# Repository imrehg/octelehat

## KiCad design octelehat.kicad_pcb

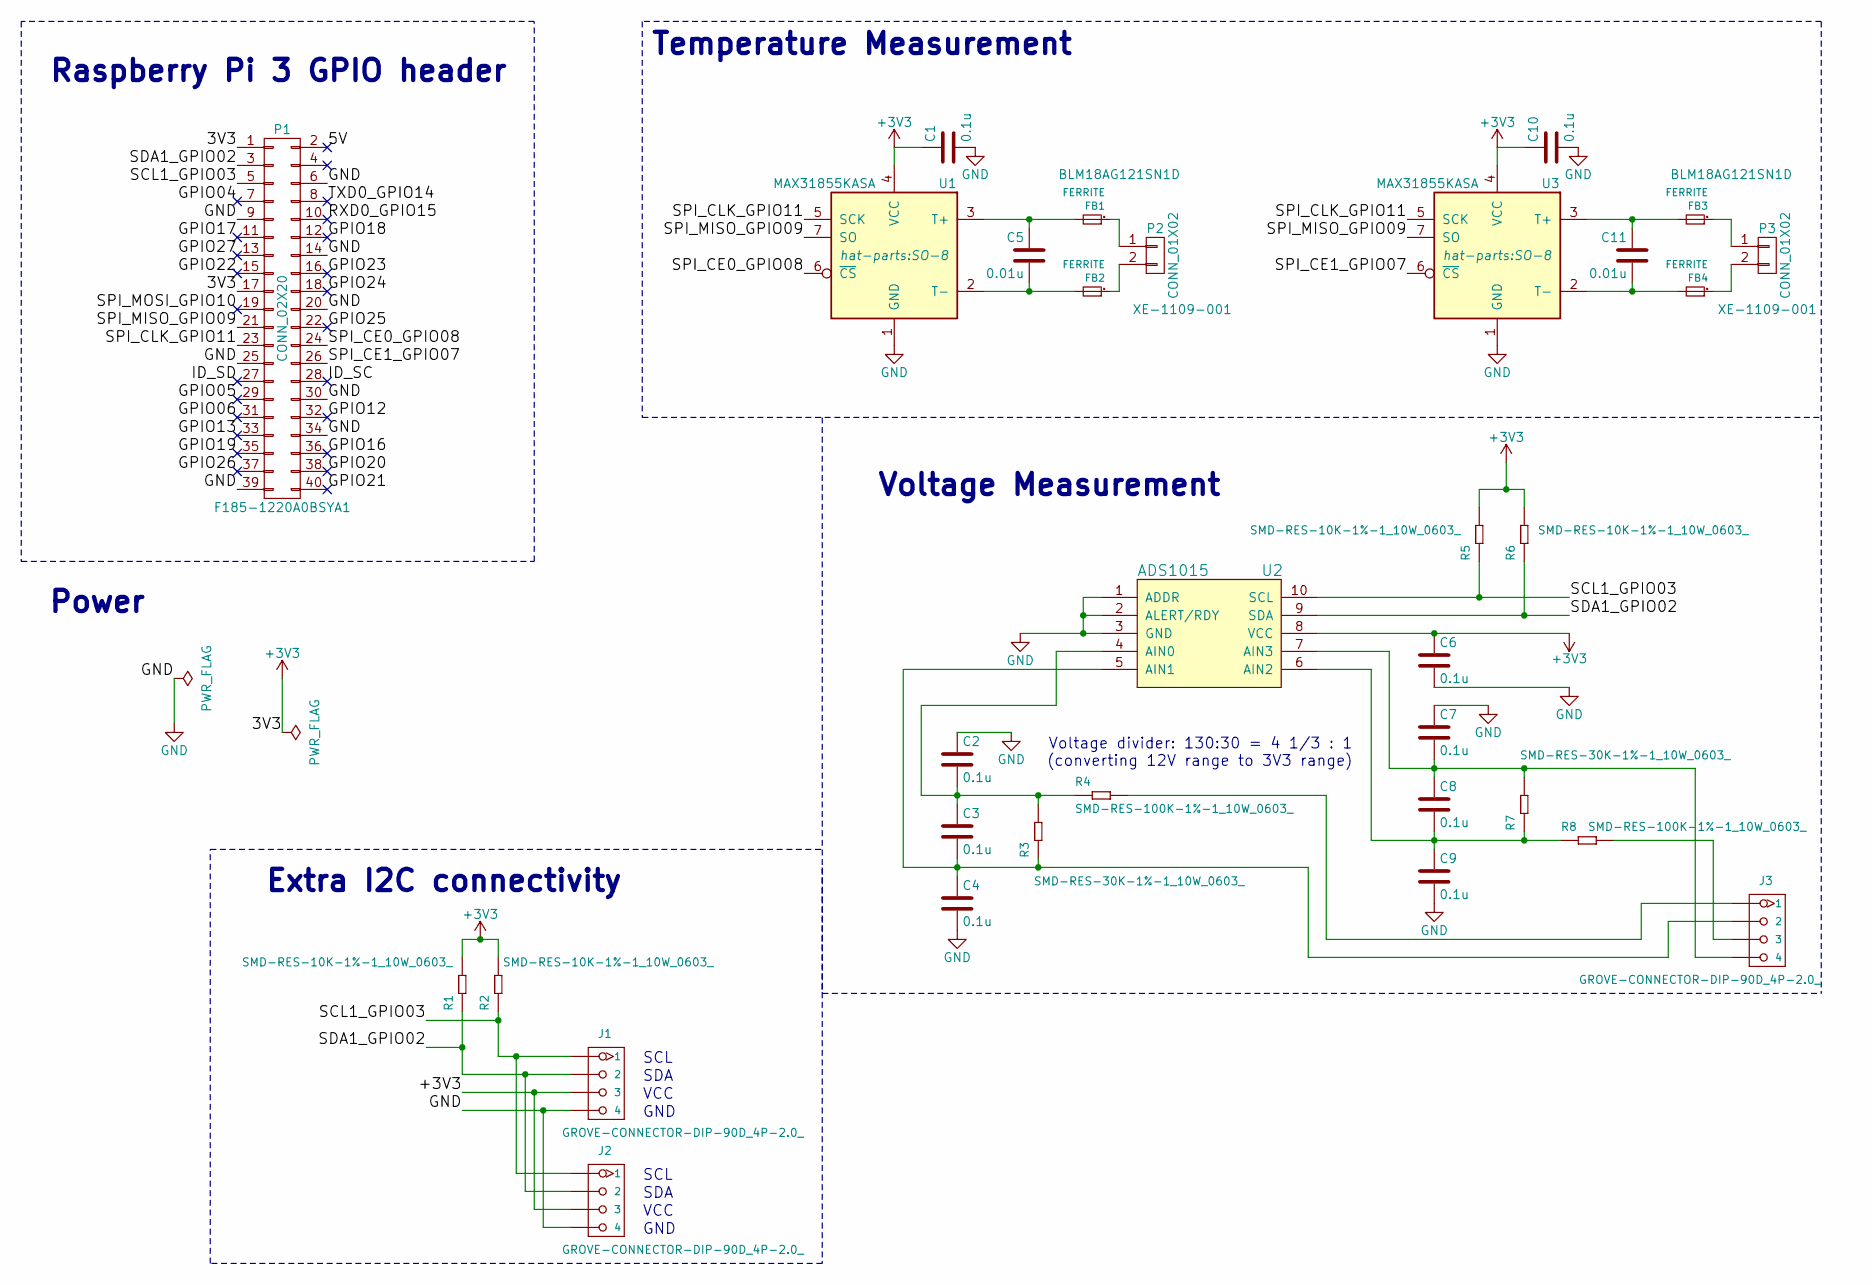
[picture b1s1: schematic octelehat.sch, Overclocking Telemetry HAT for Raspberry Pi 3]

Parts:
C1, C2, C3, C4, C6, C7, C8, C9, C10: 0.1u; C_0402; MPN CC0402KRX7R8BB104
C5, C11: 0.01u; C_0402; MPN CC0402KRX7R9BB103
FB1, FB2, FB3, FB4: FERRITE; L0603; MPN BLM18AG121SN1D
J1, J2, J3: GROVE-CONNECTOR-DIP-90D_4P-2.0_; HW4-2.0-90D; MPN 1125R-4P
P1: CONN_02X20; Socket_Strip_Straight_2x20_Pitch2.54mm; MPN F185-1220A0BSYA1
P2, P3: CONN_01X02; Thermocouple; MPN XE-1109-001
R1, R2, R5, R6: SMD-RES-10K-1%-1_10W_0603_; R0603; MPN RC0603FR-0710KL
R3, R7: SMD-RES-30K-1%-1_10W_0603_; MPN RC0603FR-0730KL
R4, R8: SMD-RES-100K-1%-1_10W_0603_; MPN RC0603FR-07100KL
U1, U3: MAX31855KASA; SO-8; MPN MAX31855KASA
U2: ADS1015; TSSOP-10_3x3mm_Pitch0.5mm; MPN ADS1015IDGSR

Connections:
+3V3: C1.1, C6.1, C10.1, J1.3, J2.3, P1.1, P1.17, R1.2, R2.2, R5.2, R6.2, U1.4 (VCC), U2.8 (VCC), U3.4 (VCC)
/5V: P1.2
/GPIO04: P1.7
/GPIO05: P1.29
/GPIO06: P1.31
/GPIO12: P1.32
/GPIO13: P1.33
/GPIO16: P1.36
/GPIO17: P1.11
/GPIO18: P1.12
/GPIO19: P1.35
/GPIO20: P1.38
/GPIO21: P1.40
/GPIO22: P1.15
/GPIO23: P1.16
/GPIO24: P1.18
/GPIO25: P1.22
/GPIO26: P1.37
/GPIO27: P1.13
/ID_SC: P1.28
/ID_SD: P1.27
/RXD0_GPIO15: P1.10
/SCL1_GPIO03: J1.1, J2.1, P1.5, R2.1, R5.1, U2.10 (SCL)
/SDA1_GPIO02: J1.2, J2.2, P1.3, R1.1, R6.1, U2.9 (SDA)
/SPI_CE0_GPIO08: P1.24, U1.6 (~CS~)
/SPI_CE1_GPIO07: P1.26, U3.6 (~CS~)
/SPI_CLK_GPIO11: P1.23, U1.5 (SCK), U3.5 (SCK)
/SPI_MISO_GPIO09: P1.21, U1.7 (SO), U3.7 (SO)
/SPI_MOSI_GPIO10: P1.19
/TXD0_GPIO14: P1.8
GND: C1.2, C2.1, C4.2, C6.2, C7.1, C9.2, C10.2, J1.4, J2.4, P1.6, P1.9, P1.14, P1.20, P1.25, P1.30, P1.34, P1.39, U1.1 (GND), U2.1 (ADDR), U2.2 (ALERT/RDY), U2.3 (GND), U3.1 (GND)
unnamed: C2.2, C3.1, R3.2, R4.1, U2.4 (AIN0)
unnamed: C3.2, C4.1, J3.2, R3.1, U2.5 (AIN1)
unnamed: C5.1, FB1.2, U1.3 (T+)
unnamed: C5.2, FB2.2, U1.2 (T-)
unnamed: C7.2, C8.1, J3.4, R7.2, U2.7 (AIN3)
unnamed: C8.2, C9.1, R7.1, R8.1, U2.6 (AIN2)
unnamed: C11.1, FB3.2, U3.3 (T+)
unnamed: C11.2, FB4.2, U3.2 (T-)
unnamed: FB1.1, P2.1
unnamed: FB2.1, P2.2
unnamed: FB3.1, P3.1
unnamed: FB4.1, P3.2
unnamed: J3.1, R4.2
unnamed: J3.3, R8.2

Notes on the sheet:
Raspberry Pi 3 GPIO header
Extra I2C connectivity
Power
Temperature Measurement
Voltage Measurement
SCL
SDA
VCC
GND
Voltage divider: 130:30 = 4 1/3 : 1 (converting 12V range to 3V3 range)

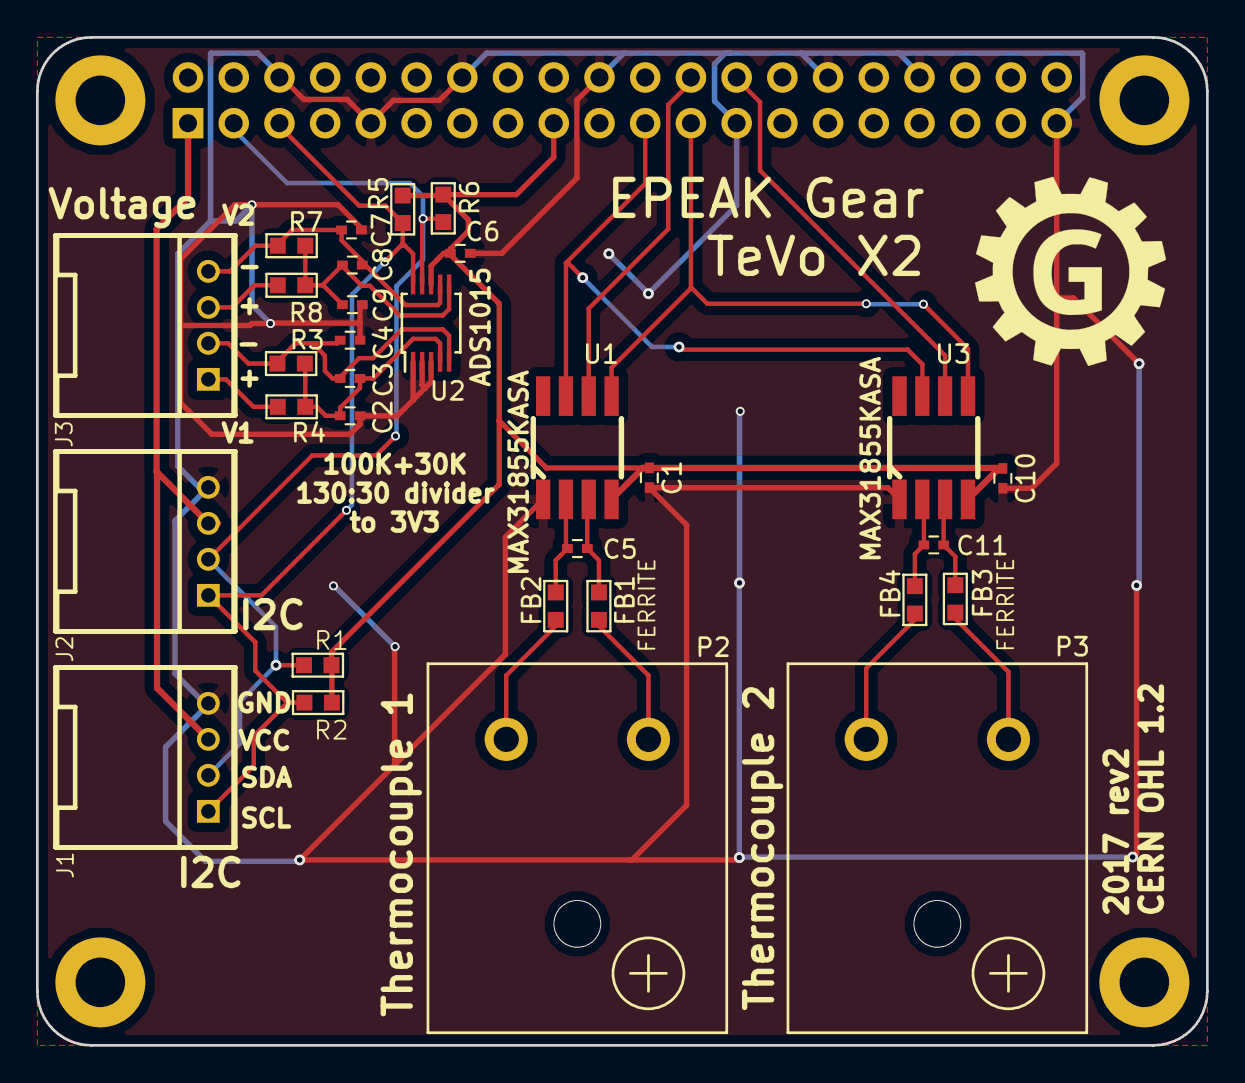
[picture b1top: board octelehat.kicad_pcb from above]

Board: 2 copper layers, 65.0 x 56.0 mm, 32 parts (1 on the bottom side), 22 nets.

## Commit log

2016-12-11 initial
2016-12-11 work in progess, schematic
2017-04-05 reassign parts for open parts library
2017-04-05 schematics changes
2017-04-05 PCB work in progress
2017-04-05 adjust design rules
2017-04-05 add extra files that might be needed
2017-04-06 work in progress
2017-04-07 rev1 routing
2017-04-07 revised
2017-04-10 design update
2017-04-10 add gerbers
2017-05-19 update voltage divider part of circuit
2017-05-19 adding changelog & updating schematics PDF
2017-06-18 updated rev2

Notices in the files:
octelehat.kicad_pcb:
CERN OHL 1.2
